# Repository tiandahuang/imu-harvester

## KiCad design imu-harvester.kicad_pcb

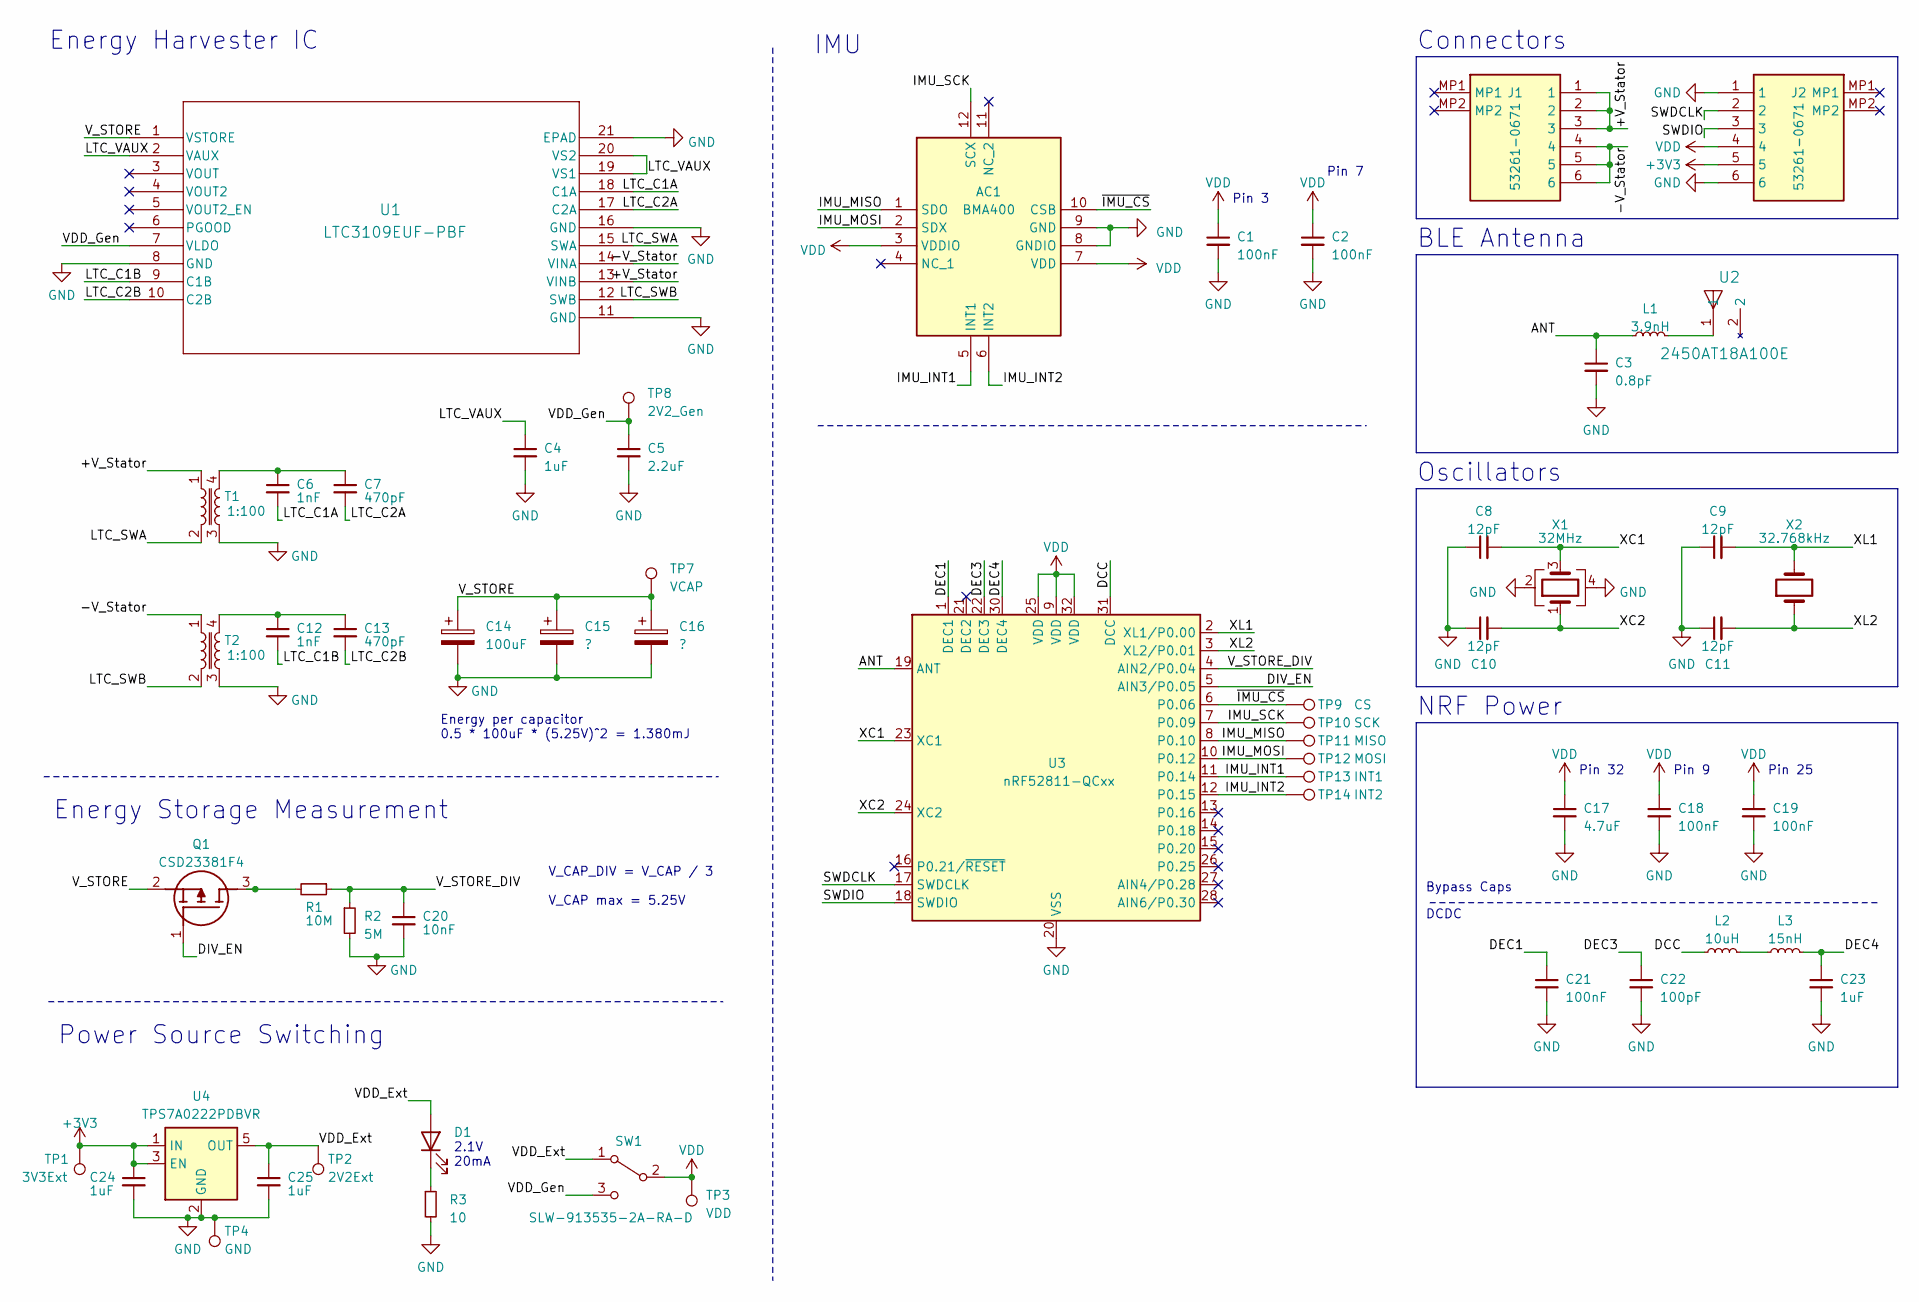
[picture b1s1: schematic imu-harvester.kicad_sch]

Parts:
AC1: BMA400; BOSCH_LGA-12; Mouser Part Number 262-BMA400
C1, C2, C18, C19, C21: 100nF; C_0402_1005Metric; Manufacturer_Part_Number KGM05AR71C104KN
C3: 0.8pF; C_0402_1005Metric; Manufacturer_Part_Number GRM1555C1ER80BA01D
C4, C23, C24, C25: 1uF; C_0402_1005Metric; Manufacturer_Part_Number CM05X7R105K06AH-HE
C5: 2.2uF; C_0402_1005Metric; Manufacturer_Part_Number GRM155Z71A225KE01D
C6, C12: 1nF; C_0402_1005Metric; Manufacturer_Part_Number C0402C102KCRACAUTO
C7, C13: 470pF; C_0402_1005Metric; Manufacturer_Part_Number KGM05ACG1H471JH
C8, C9, C10, C11: 12pF; C_0402_1005Metric; Manufacturer_Part_Number KGM05ACG1H120JN
C14: 100uF; CP_EIA-6032-28_Kemet-C; Manufacturer_Part_Number TL3C107K010C0200
C15, C16: ?; CP_EIA-6032-28_Kemet-C
C17: 4.7uF; C_0603_1608Metric; Manufacturer_Part_Number GRM188Z71C475KE21D
C20: 10nF; C_0402_1005Metric; Manufacturer_Part_Number C0402C103K1RACAUTO
C22: 100pF; C_0402_1005Metric; Manufacturer_Part_Number KGM05ACG1H101JN
D1: LO Q976.01-P2R2-25-1; LED_0603_1608Metric; Manufacturer_Part_Number LO Q976.01-P2R2-25-1
J1, J2: 53261-0671; 532610671; Mouser Part Number 538-53261-0671
L1: 3.9nH; L_0402_1005Metric; Manufacturer_Part_Number LQG15WZ3N9B02D
L2: 10uH; L_0603_1608Metric; Manufacturer_Part_Number KLZ1608MHR100WTD25
L3: 15nH; L_0402_1005Metric; Manufacturer_Part_Number LQG15WZ15NG02D
Q1: CSD23381F4; Mouser Part Number 595-CSD23381F4
R1: 10M; R_0402_1005Metric; Manufacturer_Part_Number RCC040210M0FKED
R2: 5M; R_0402_1005Metric; Manufacturer_Part_Number CRCW04024M99FKED
R3: 10; R_0402_1005Metric; Manufacturer_Part_Number RCC040210R0FKED
SW1: SLW-913535-2A-RA-D; Manufacturer_Part_Number SLW-913535-2A-RA-D
T1, T2: 1:100; 74488540070; Manufacturer_Part_Number 74488540070
TP1: 3V3Ext; Testpoint_Hex_D3.0
TP2: 2V2Ext; Testpoint_Hex_D3.0
TP3: VDD; Testpoint_Hex_D3.0
TP4: GND; Testpoint_Hex_D3.0
TP7: VCAP; TestPoint_Pad_D1.0mm
TP8: 2V2_Gen; TestPoint_Pad_D1.0mm
TP9: CS; TestPoint_Pad_D1.0mm
TP10: SCK; TestPoint_Pad_D1.0mm
TP11: MISO; TestPoint_Pad_D1.0mm
TP12: MOSI; TestPoint_Pad_D1.0mm
TP13: INT1; TestPoint_Pad_D1.0mm
TP14: INT2; TestPoint_Pad_D1.0mm
U1: LTC3109EUF-PBF; QFN-20_UF_LIT; Manufacturer_Part_Number LTC3109EUF#PBF
U2: 2450AT18A100E; 2450AT18A100E_JOT; Manufacturer_Part_Number 2450AT18A100E
U3: nRF52811-QCxx; QFN-32-1EP_5x5mm_P0.5mm_EP3.6x3.6mm_ThermalVias; Manufacturer_Part_Number nRF52811-QCAA-R
U4: TPS7A0222PDBVR; SOT-23-5; Manufacturer_Part_Number TPS7A0222PDBVR
X1: 32MHz; Crystal_SMD_2016-4Pin_2.0x1.6mm; Manufacturer_Part_Number ECS-320-8-37B2-JTY-TR
X2: 32.768kHz; Crystal_SMD_2012-2Pin_2.0x1.2mm; Manufacturer_Part_Number ECS-.327-9-12R-TR

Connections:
+3V3: C24.1, J2.5, TP1.1, U4.1 (IN), U4.3 (EN)
/+V_Stator: J1.1, J1.2, J1.3, T1.1, U1.13 (VINB)
/-V_Stator: J1.4, J1.5, J1.6, T2.1, U1.14 (VINA)
/ANT: C3.1, L1.1, U3.19 (ANT)
/DCC: L2.1, U3.31 (DCC)
/DEC1: C21.1, U3.1 (DEC1)
/DEC3: C22.1, U3.22 (DEC3)
/DEC4: C23.1, L3.2, U3.30 (DEC4)
/DIV_EN: Q1.1 (G), U3.5 (AIN3/P0.05)
/IMU_INT1: AC1.5 (INT1), TP13.1, U3.11 (P0.14)
/IMU_INT2: AC1.6 (INT2), TP14.1, U3.12 (P0.15)
/IMU_MISO: AC1.1 (SDO), TP11.1, U3.8 (P0.10)
/IMU_MOSI: AC1.2 (SDX), TP12.1, U3.10 (P0.12)
/IMU_SCK: AC1.12 (SCX), TP10.1, U3.7 (P0.09)
/LTC_C1A: C6.2, U1.18 (C1A)
/LTC_C1B: C12.2, U1.9 (C1B)
/LTC_C2A: C7.2, U1.17 (C2A)
/LTC_C2B: C13.2, U1.10 (C2B)
/LTC_SWA: T1.2, U1.15 (SWA)
/LTC_SWB: T2.2, U1.12 (SWB)
/LTC_VAUX: C4.1, U1.2 (VAUX), U1.19 (VS1), U1.20 (VS2)
/SWDCLK: J2.2, U3.17 (SWDCLK)
/SWDIO: J2.3, U3.18 (SWDIO)
/VDD_Ext: C25.1, D1.2 (A), SW1.1 (A), TP2.1, U4.5 (OUT)
/VDD_Gen: C5.1, SW1.3 (C), TP8.1, U1.7 (VLDO)
/V_STORE: C14.1, C15.1, C16.1, Q1.2 (S), TP7.1, U1.1 (VSTORE)
/V_STORE_DIV: C20.1, R1.1, R2.1, U3.4 (AIN2/P0.04)
/XC1: C8.2, U3.23 (XC1), X1.3
/XC2: C10.2, U3.24 (XC2), X1.1
/XL1: C9.2, U3.2 (XL1/P0.00), X2.2
/XL2: C11.2, U3.3 (XL2/P0.01), X2.1
/~IMU_CS: AC1.10 (CSB), TP9.1, U3.6 (P0.06)
GND: AC1.8 (GNDIO), AC1.9 (GND), C1.2, C2.2, C3.2, C4.2, C5.2, C8.1, C9.1, C10.1, C11.1, C14.2, C15.2, C16.2, C17.2, C18.2, C19.2, C20.2, C21.2, C22.2, C23.2, C24.2, C25.2, J2.1, J2.6, R2.2, R3.2, T1.3, T2.3, TP4.1, U1.8 (GND), U1.11 (GND), U1.16 (GND), U1.21 (EPAD), U3.20 (VSS), U3.29 (VSS), U3.33 (VSS), U4.2 (GND), X1.2, X1.4
unnamed: C6.1, C7.1, T1.4
unnamed: C12.1, C13.1, T2.4
unnamed: D1.1 (K), R3.1
unnamed: L1.2, U2.1
unnamed: L2.2, L3.1
unnamed: Q1.3 (D), R1.2
VDD: AC1.3 (VDDIO), AC1.7 (VDD), C1.1, C2.1, C17.1, C18.1, C19.1, J2.4, SW1.2 (B), TP3.1, U3.9 (VDD), U3.25 (VDD), U3.32 (VDD)

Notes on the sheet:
V_CAP_DIV = V_CAP / 3 V_CAP max = 5.25V
Energy Storage Measurement
Pin 3
Power Source Switching
Pin 9
NRF Power
Connectors
DCDC
IMU
2.1V 20mA
Bypass Caps
BLE Antenna
Oscillators
Energy per capacitor 0.5 * 100uF * (5.25V)^2 = 1.380mJ
Pin 32
Pin 25
Energy Harvester IC
Pin 7

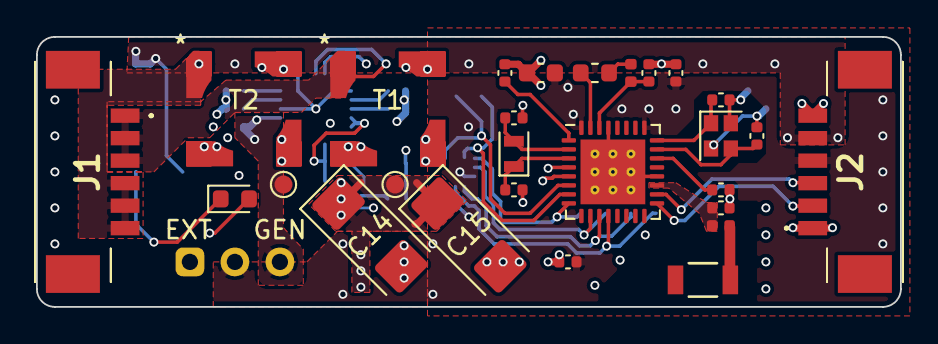
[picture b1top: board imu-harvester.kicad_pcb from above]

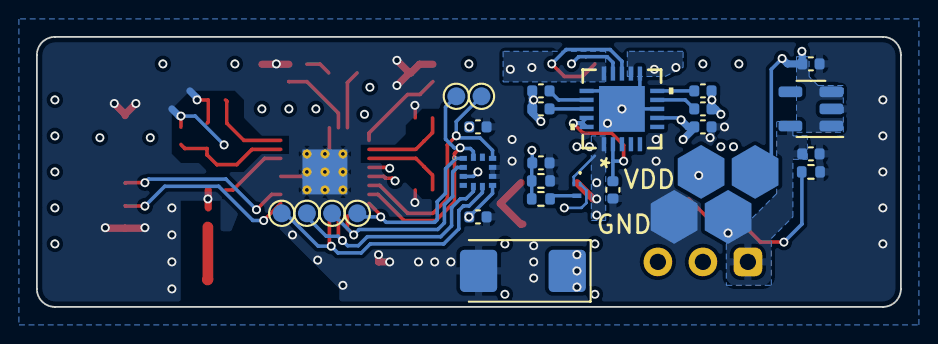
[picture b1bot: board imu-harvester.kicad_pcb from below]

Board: 4 copper layers, 48.0 x 15.0 mm, 57 parts (29 on the bottom side), 40 nets.

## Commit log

2024-01-19 schematic done
2024-01-19 big cap and transformer
2024-01-22 parts
2024-01-22 place
2024-01-22 route
2024-01-23 bom & gerbers
2024-02-09 gerbers 2
2024-02-23 3d models
2024-02-24 photos
